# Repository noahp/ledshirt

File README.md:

# Ledshirt Readme
Battery powered LED flasher.

# Block Diagram

# 3d Renders

# Parts
|Item|Link|
|----|----|
|Charger|http://ww1.microchip.com/downloads/en/DeviceDoc/21984e.pdf<br/>http://www.microchip.com/wwwproducts/Devices.aspx?dDocName=en024903|
|12v Boost|http://www.digikey.com/product-detail/en/AP3012KTR-G1/AP3012KTR-G1DICT-ND/4505297<br/>http://www.diodes.com/catalog/Boost_Converter_44/AP3012_9395|
|Diode|http://www.mouser.com/Search/ProductDetail.aspx?qs=NQ47qNm99eDyWTEd07miYA%3d%3d|
|Inductor|http://www.digikey.com/product-detail/en/SRR6038-100Y/SRR6038-100YCT-ND/2127571|
|Micro|pic12f1822 [Microchip product page](http://www.microchip.com/wwwproducts/Devices.aspx?dDocName=en544839)<br/>http://www.digikey.com/product-search/en?keywords=PIC12F1822-I%2FSN|
|LEDs|Original cree bare emitters-<br/>http://www.digikey.com/product-detail/en/CLM1B-GKW-CVAXA7A3/CLM1B-GKW-CVAXA7A3CT-ND/3659979<br/>New flexible waterproof strip-<br/>http://www.ebay.com/itm/321843596089?_trksid=p2060353.m2749.l2649&ssPageName=STRK%3AMEBIDX%3AIT|
|FET|P-N SOT23-6<br/>http://www.digikey.com/product-detail/en/DMC2038LVT-7/DMC2038LVT-7DICT-ND/2756074|
|Pushbutton|http://www.digikey.com/product-detail/en/PTS645SK50SMTR92%20LFS/CKN9087CT-ND/1146813|
|USB Micro B|http://www.mouser.com/ProductDetail/FCI/10118192-0001LF|
|Enclosure|Possible options-<br/>http://www.mouser.com/ProductDetail/Bud-Industries/HH-3490<br/>http://www.mouser.com/ProductDetail/New-Age-Enclosures/S3A-202010|

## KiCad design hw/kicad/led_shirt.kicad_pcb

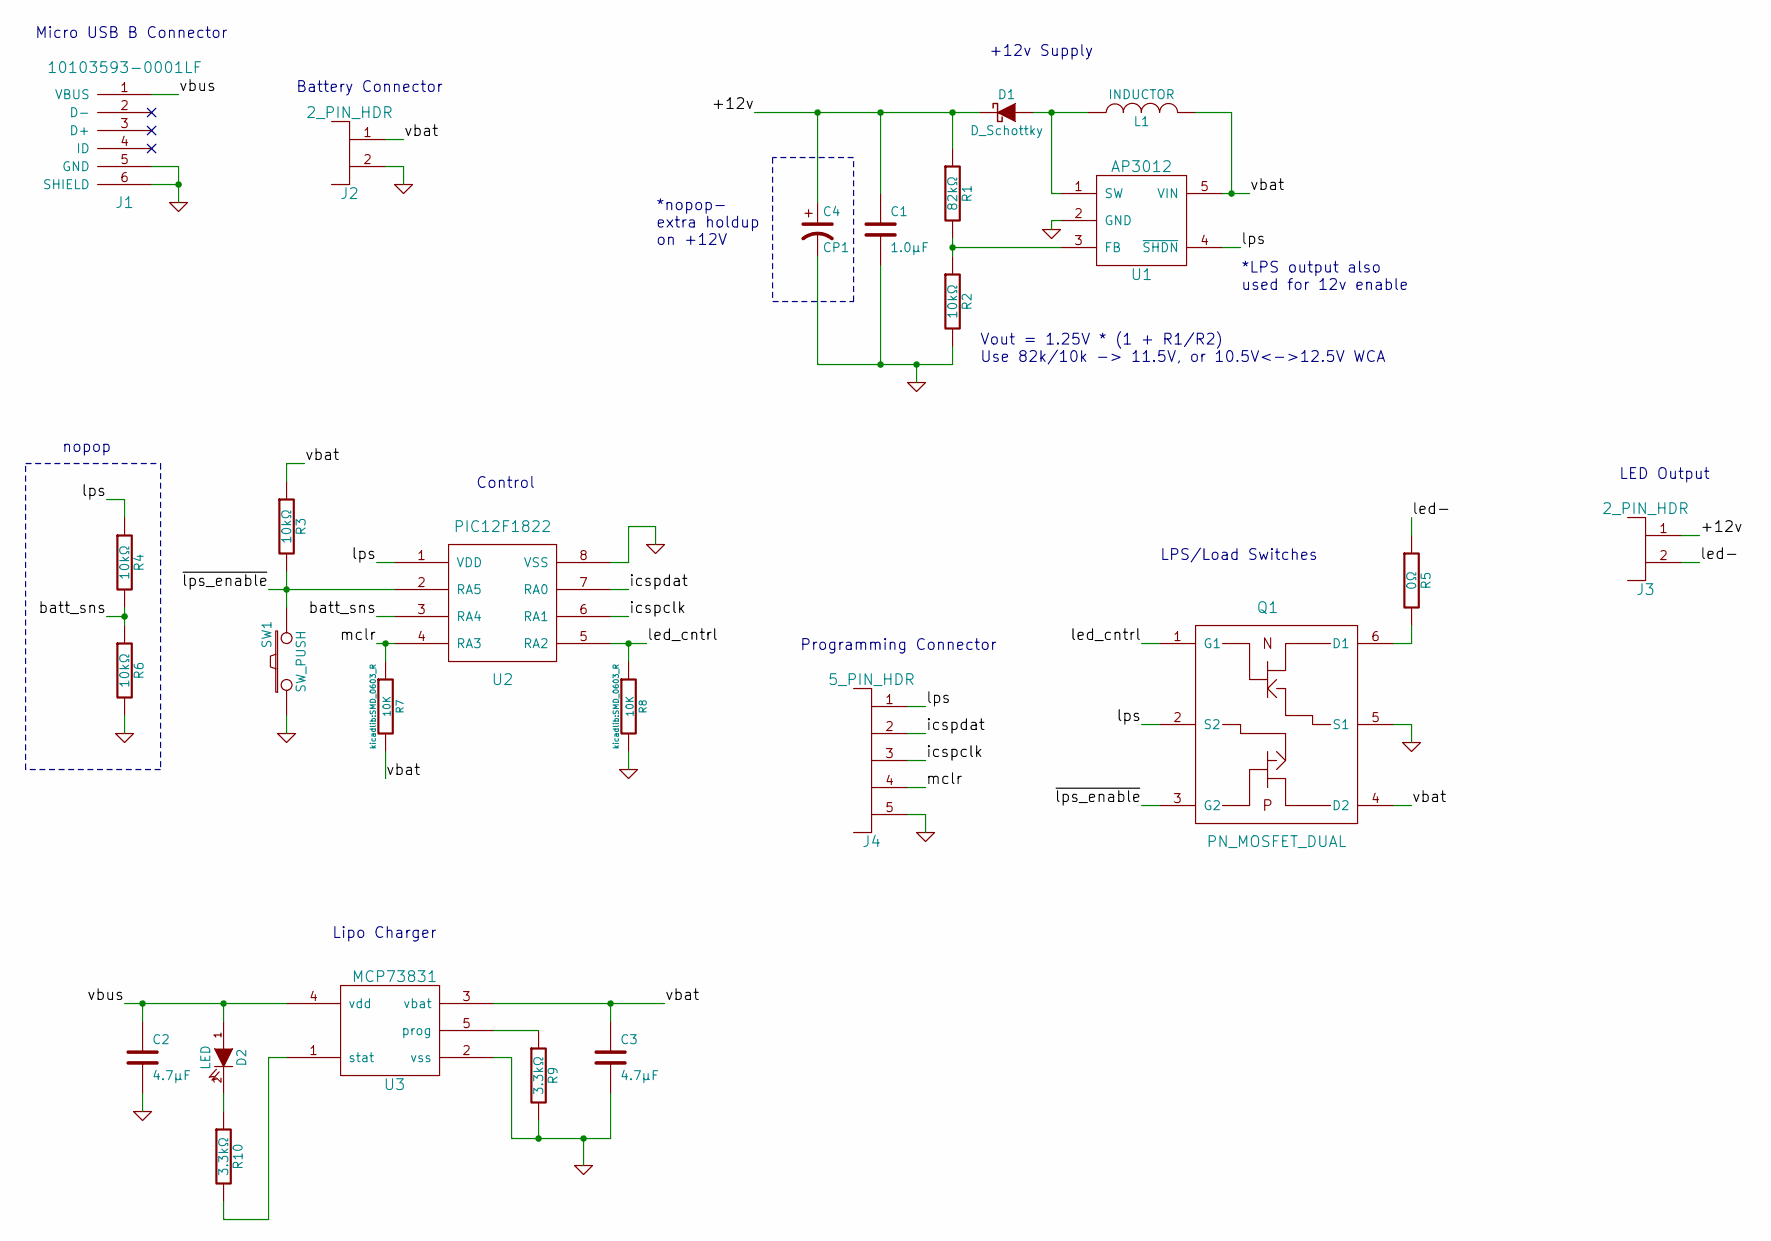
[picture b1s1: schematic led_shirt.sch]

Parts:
C1: 1.0µF; SMD_0603_R
C2, C3: 4.7µF; SMD_0603_R
C4: CP1; SMD_5X5.2_CAP
D1: D_Schottky; SMD_SOD-123_DIODE
D2: LED; SMD_0603_LED
J1: 10103593-0001LF; usb_micro_b_smt
J2, J3: 2_PIN_HDR; TH_JST_2PIN_RIGHTANGLE
J4: 5_PIN_HDR; SMD_JST_5_PIN_VERT
L1: INDUCTOR; SMD_IND_6.8x6.8_SRR6038-100Y
Q1: PN_MOSFET_DUAL; SMD_SOT23-6
R1: 82kΩ; SMD_0603_R
R2, R3, R4, R6: 10kΩ; SMD_0603_R
R5: 0Ω; SMD_0603_R
R7, R8: 10K; SMD_0603_R
R9, R10: 3.3kΩ; SMD_0603_R
SW1: SW_PUSH; spst_pushbutton_smd
U1: AP3012; SMD_SOT23-5
U2: PIC12F1822; SMD_SOIC-8
U3: MCP73831; SMD_SOT23-5

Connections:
/+12v: C1.1, C4.1, D1.1 (K), J3.1, R1.1
/batt_sns: R4.2, R6.1, U2.3 (RA4)
/icspclk: J4.3, U2.6 (RA1)
/icspdat: J4.2, U2.7 (RA0)
/led-: J3.2, R5.1
/led_cntrl: Q1.1 (G1), R8.1, U2.5 (RA2)
/lps: J4.1, Q1.2 (S2), R4.1, U1.4 (~SHDN), U2.1 (VDD); also elsewhere on the board
/mclr: J4.4, R7.1, U2.4 (RA3)
/vbat: C3.1, J2.1, L1.2, Q1.4 (D2), R3.1, R7.2, U1.5 (VIN), U3.3 (vbat)
/vbus: C2.1, D2.1 (A), J1.1 (VBUS), U3.4 (vdd)
/~lps_enable: Q1.3 (G2), R3.2, SW1.2, U2.2 (RA5)
GND: C1.2, C2.2, C3.2, C4.2, J1.5 (GND), J1.6 (SHIELD), J2.2, J4.5, Q1.5 (S1), R2.2, R6.2, R8.2, R9.2, SW1.1, U1.2 (GND), U2.8 (VSS), U3.2 (vss); also elsewhere on the board
unnamed: D1.2 (A), L1.1, U1.1 (SW)
unnamed: D2.2 (K), R10.1
unnamed: Q1.6 (D1), R5.2
unnamed: R1.2, R2.1, U1.3 (FB)
unnamed: R9.1, U3.5 (prog)
unnamed: R10.2, U3.1 (stat)

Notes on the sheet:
Lipo Charger
Control
nopop
Micro USB B Connector
Battery Connector
Programming Connector
*LPS output also used for 12v enable
+12v Supply
LED Output
LPS/Load Switches
*nopop- extra holdup on +12V
Vout = 1.25V * (1 + R1/R2) Use 82k/10k -> 11.5V, or 10.5V<->12.5V WCA

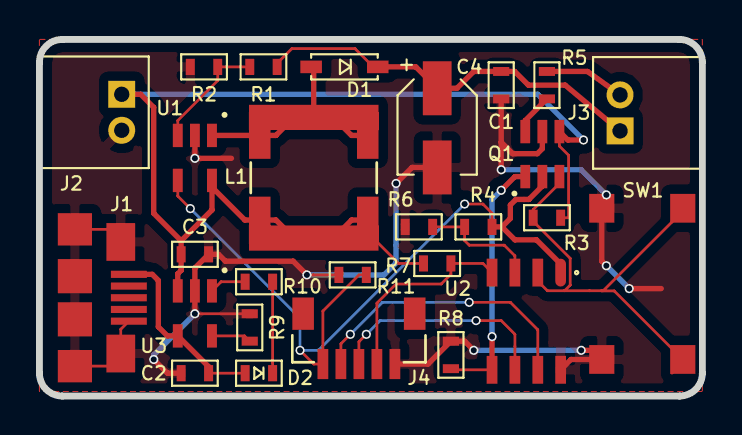
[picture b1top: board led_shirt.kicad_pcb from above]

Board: 2 copper layers, 36.8 x 19.8 mm, 27 parts (0 on the bottom side), 18 nets.

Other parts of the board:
R11: 10K; SMD_0603_R

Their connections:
/lps: R11.1; also elsewhere on the board
GND: R11.2; also elsewhere on the board

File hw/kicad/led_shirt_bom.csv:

Value,Ref,Footprint
10k,R3,kicadlib:SMD_0603_R
0,R5,kicadlib:SMD_0603_R
4.7F,C3,kicadlib:SMD_0603_R
3.3k,R9,kicadlib:SMD_0603_R
3.3k,R10,kicadlib:SMD_0603_R
LED,D2,kicadlib:SMD_0603_LED
4.7F,C2,kicadlib:SMD_0603_R
10103593-0001LF,J1,kicadlib:usb_micro_b_smt
MCP73831,U3,kicadlib:SMD_SOT23-5
PIC12F1822,U2,kicadlib:SMD_SOIC-8
10K,R7,kicadlib:SMD_0603_R
10K,R8,kicadlib:SMD_0603_R
SW_PUSH,SW1,kicadlib:spst_pushbutton_smd
PN_MOSFET_DUAL,Q1,kicadlib:SMD_SOT23-6
AP3012,U1,kicadlib:SMD_SOT23-5
5_PIN_HDR,J4,kicadlib:SMD_JST_5_PIN_VERT
10k,R4,kicadlib:SMD_0603_R
10k,R6,kicadlib:SMD_0603_R
D_Schottky,D1,kicadlib:SMD_SOD-123_DIODE
INDUCTOR,L1,kicadlib:SMD_IND_6.8x6.8_SRR6038-100Y
2_PIN_HDR,J2,kicadlib:TH_JST_2PIN_RIGHTANGLE
82k,R1,kicadlib:SMD_0603_R
10k,R2,kicadlib:SMD_0603_R
1.0F,C1,kicadlib:SMD_0603_R
2_PIN_HDR,J3,kicadlib:TH_JST_2PIN_RIGHTANGLE
CP1,C4,kicadlib:SMD_5X5.2_CAP
10K,R11,kicadlib:SMD_0603_R

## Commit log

2012-12-11 - add all from bitbucket
2012-12-11 - add images to wiki
2012-12-11 - fix image urls
2012-12-11 - add pictures of the pcb
2012-12-11 - fix pcb pic url ref
2012-12-11 - comment about pic footprint issue
2012-12-12 - change footprint for pic to tssop-14 (was soic-14)
2012-12-12 - add pic of charging
2012-12-12 - remove metadata from jpeg's
2012-12-14 - add basic empty project.
2012-12-16 - save initial test code. - add hex file
2012-12-18 - timer interrupt working
2012-12-19 - use tmr1 int for "pwm", tmr0 for on/off & button debounce (may move button debounce to tmr2? or speed up timr0)
2012-12-21 - use pwm hw instead of tmr1 for driving the leds.
2012-12-24 - add pwm4
2013-10-18 switch to pic12f1822
2013-10-18 add new pcb
2013-10-18 remove old board file
2013-10-18 rev 2 board done
2013-10-22 update gerbys.
2013-10-22 - update renders
2013-10-22 add sch.
2013-10-23 - add 10k pullup to mclr and 10k pulldown to fet gate (startup sequencing)
2013-10-23 - update pcb & gerbers with new pullups
2013-10-23 - update sch & pcb screengrabs. add pdf of schematic.
2013-10-27 add leds to onboard
2013-10-27 update netlist
2013-10-27 add led footprints and add them to pcb
2013-11-05 remove
2013-11-05 - cleanup - add led's to schematic instead of test point breakout
2013-11-05 - add kicadlib
2013-11-06 - add plcc2 footprint & make cmplist
2013-11-06 - start layout
2013-11-07 - two sides! also delete programming pins, who needs 'em
2013-11-08 work on pcb
2013-11-08 new pcb
2013-11-08 - ordered
2013-11-08 - missed something
2013-11-23 - switch config from PIC16F1503 to PIC12F1822
2013-11-23 - works
2013-11-23 - add pwm, works
2013-11-25 - reduce pwm freq. to 50kHz from 100kHz to drop power loss in fet
2013-11-25 - move charge led to front >_<
2015-10-30 save some changes. need to switch to dual n-fet package.
2015-10-30 add dual fet symbol
2015-10-30 fix up fet symbol and connect it
2015-11-03 update sch
2015-11-10 fix labels
2015-11-10 finish sch, add bom
2015-11-11 more components
2015-11-12 footprints mostly done, some missing modules
2015-11-12 add usb micro b model
2015-11-20 parts positioned, silks. next is traces.
2015-11-20 layout done
2015-11-20 add screw mounts, which adds $1.60 to osh price. also need to reposition usb connector if I use screw mounts.
2015-11-20 update 12v boost feedback resistor divider
2015-11-21 add 3d renders
2015-11-22 save gerbers and new renders
2015-11-22 update gerbers zip
2015-11-22 refresh gerbers.
2015-12-18 add hw block diagram
2015-12-18 rename so github markdown can render it
2015-12-18 add button to block diagram
2015-12-18 add add pull-down to lps net, to prevent p-fet leakage from enabling 12v boost when lps is disabled
2016-05-08 led on by default, adjust blink mode to lower duty cycle, disable button
2016-05-14 new kicadlib
